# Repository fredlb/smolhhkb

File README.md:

# smolhhkb
A small 40% keyboard with same asymetrical bottom row as hhkb.

Pictured is a one-off prototype:  
Top: Polycarbonate  
Bottom: Aluminium, white anodization  
Weight: Copper  

The little window down to the PCB is resin printed, with an oring to attach it to the top piece.

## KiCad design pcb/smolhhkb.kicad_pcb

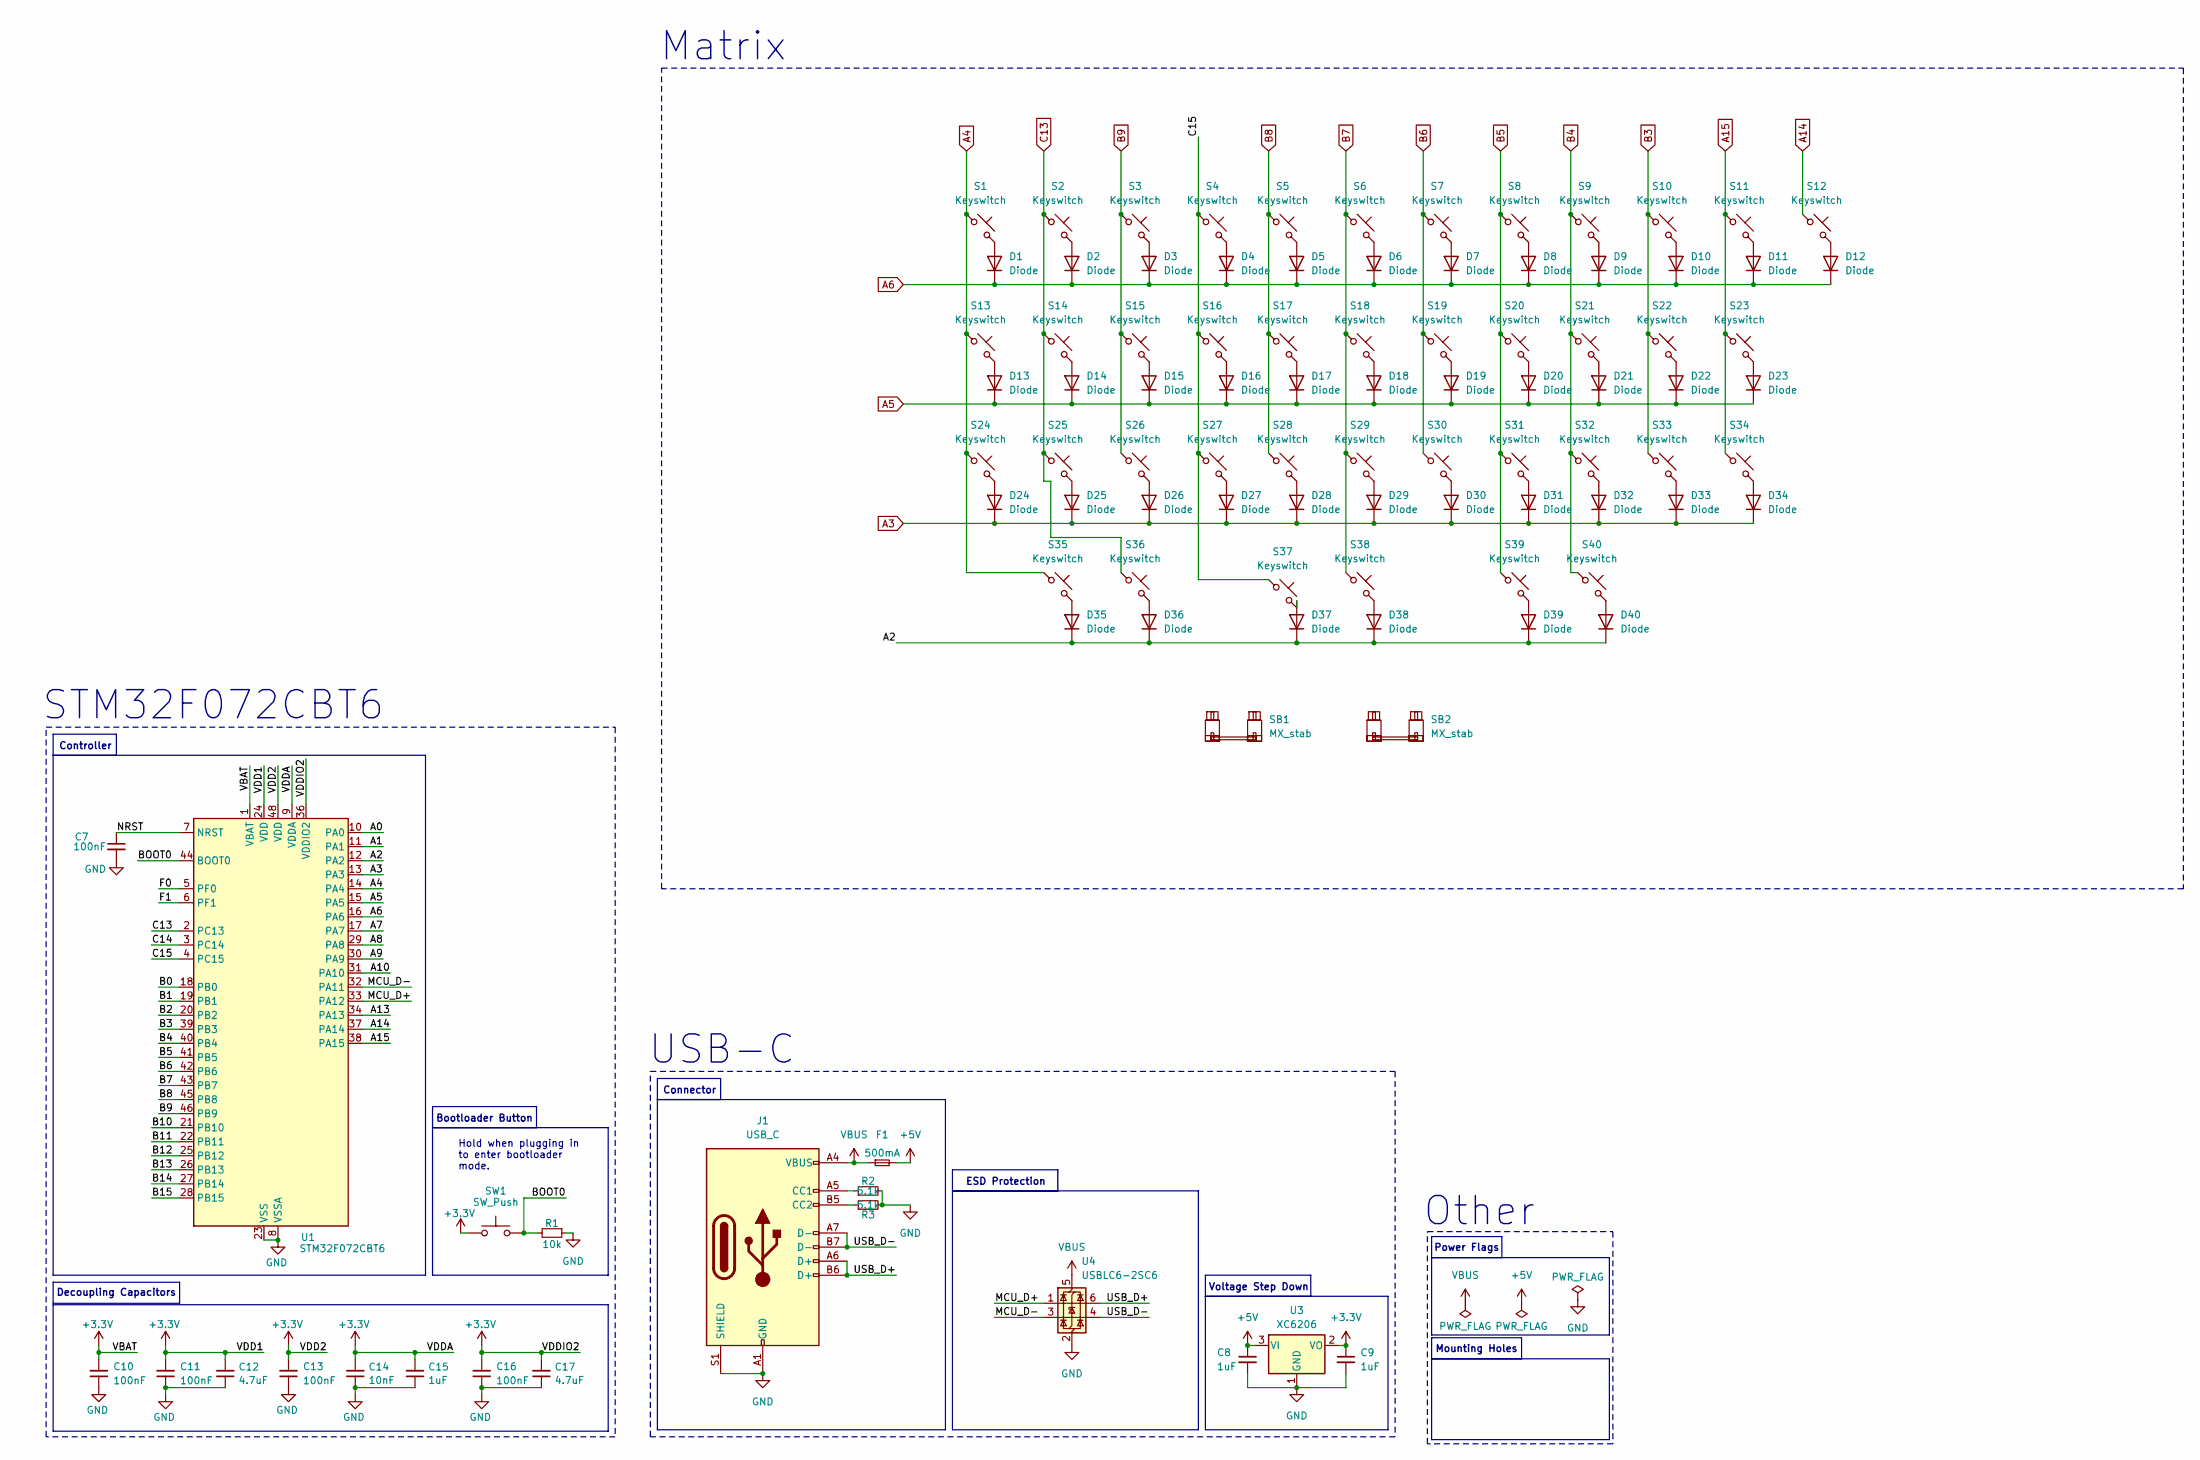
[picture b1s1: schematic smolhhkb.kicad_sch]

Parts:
C7: 100nF; Capacitor_0402; LCSC C307331
C8, C9: 1uF; Capacitor_0402; LCSC C52923
C10, C11, C13, C16: 100nF; Capacitor_0402; MPN CL05B104KB54PNC; LCSC C307331
C12, C17: 4.7uF; Capacitor_0402; MPN CL05A475MP5NRNC; LCSC C23733
C14: 10nF; Capacitor_0402; MPN CL05B103KB5NNNC; LCSC C15195
C15: 1uF; Capacitor_0402; MPN CL05A105KA5NQNC; LCSC C52923
D1, D2, D3, D4, D5, D6, D7, D8, D9, D10, D11, D12, D13, D14, D15, D16, D17, D18, D19, D20, D21, D22, D23, D24, D25, D26, D27, D28, D29, D30, D31, D32, D33, D34, D35, D36, D37, D38, D39, D40: Diode; Diode_SOD-123
F1: 500mA; Fuse_0603; LCSC C210357
J1: USB_C; USB_C_HRO_TYPE-C-31-M-12; LCSC C165948
R1: 10k; Resistor_0402; LCSC C25744
R2, R3: 5.1k; Resistor_0402; LCSC C25905
S1, S2, S3, S4, S5, S6, S7, S8, S9, S10, S11, S12, S14, S15, S16, S17, S18, S19, S20, S21, S22, S25, S26, S27, S28, S29, S30, S31, S32, S34, S35, S37, S38, S40: Keyswitch; SW_MX_1u
S13, S33, S36, S39: Keyswitch; SW_MX_1.25u
S23, S24: Keyswitch; SW_MX_1.75u
SB1: MX_stab; STAB_MX_2.25u
SB2: MX_stab; STAB_MX_2u
SW1: SW_Push; Button_TL3342; LCSC C115351
U1: STM32F072CBT6; Package_LQFP-48_7x7mm_P0.5; LCSC C81720
U3: XC6206; Voltage_SOT-23; LCSC C5446
U4: USBLC6-2SC6; ESD_SOT-23-6; LCSC C2827654

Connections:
+3.3V: C9.1, C10.2, C11.2, C12.2, C13.2, C14.2, C15.2, C16.2, C17.2, SW1.1, U1.1 (VBAT), U1.9 (VDDA), U1.24 (VDD), U1.36 (VDDIO2), U1.48 (VDD), U3.2 (VO)
+5V: C8.1, F1.2, U3.3 (VI)
/A0: U1.10 (PA0)
/A1: U1.11 (PA1)
/A2: D35.1 (K), D36.1 (K), D37.1 (K), D38.1 (K), D39.1 (K), D40.1 (K), U1.12 (PA2)
/A7: U1.17 (PA7)
/A8: U1.29 (PA8)
/A9: U1.30 (PA9)
/A10: U1.31 (PA10)
/A13: U1.34 (PA13)
/B0: U1.18 (PB0)
/B1: U1.19 (PB1)
/B2: U1.20 (PB2)
/B10: U1.21 (PB10)
/B11: U1.22 (PB11)
/B12: U1.25 (PB12)
/B13: U1.26 (PB13)
/B14: U1.27 (PB14)
/B15: U1.28 (PB15)
/BOOT0: R1.2, SW1.2, U1.44 (BOOT0)
/C14: U1.3 (PC14)
/C15: S4.1, S16.1, S27.1, S37.1, U1.4 (PC15)
/F0: U1.5 (PF0)
/F1: U1.6 (PF1)
/MCU_D+: U1.33 (PA12), U4.1 (I/O1)
/MCU_D-: U1.32 (PA11), U4.3 (I/O2)
/NRST: C7.1, U1.7 (NRST)
/USB_D+: J1.A6 (D+), J1.B6 (D+), U4.6 (I/O1)
/USB_D-: J1.A7 (D-), J1.B7 (D-), U4.4 (I/O2)
A3: D24.1 (K), D25.1 (K), D26.1 (K), D27.1 (K), D28.1 (K), D29.1 (K), D30.1 (K), D31.1 (K), D32.1 (K), D33.1 (K), D34.1 (K), U1.13 (PA3)
A4: S1.1, S13.1, S24.1, S35.1, U1.14 (PA4)
A5: D13.1 (K), D14.1 (K), D15.1 (K), D16.1 (K), D17.1 (K), D18.1 (K), D19.1 (K), D20.1 (K), D21.1 (K), D22.1 (K), D23.1 (K), U1.15 (PA5)
A6: D1.1 (K), D2.1 (K), D3.1 (K), D4.1 (K), D5.1 (K), D6.1 (K), D7.1 (K), D8.1 (K), D9.1 (K), D10.1 (K), D11.1 (K), D12.1 (K), U1.16 (PA6)
A14: S12.1, U1.37 (PA14)
A15: S11.1, S23.1, S34.1, U1.38 (PA15)
B3: S10.1, S22.1, S33.1, U1.39 (PB3)
B4: S9.1, S21.1, S32.1, S40.1, U1.40 (PB4)
B5: S8.1, S20.1, S31.1, S39.1, U1.41 (PB5)
B6: S7.1, S19.1, S30.1, U1.42 (PB6)
B7: S6.1, S18.1, S29.1, S38.1, U1.43 (PB7)
B8: S5.1, S17.1, S28.1, U1.45 (PB8)
B9: S3.1, S15.1, S26.1, U1.46 (PB9)
C13: S2.1, S14.1, S25.1, S36.1, U1.2 (PC13)
GND: C7.2, C8.2, C9.2, C10.1, C11.1, C12.1, C13.1, C14.1, C15.1, C16.1, C17.1, J1.A1 (GND), J1.A12 (GND), J1.B1 (GND), J1.B12 (GND), J1.S1 (SHIELD), R1.1, R2.2, R3.2, U1.8 (VSSA), U1.23 (VSS), U1.35 (VSS), U1.47 (VSS), U3.1 (GND), U4.2 (GND)
unnamed: D1.2 (A), S1.2
unnamed: D2.2 (A), S2.2
unnamed: D3.2 (A), S3.2
unnamed: D4.2 (A), S4.2
unnamed: D5.2 (A), S5.2
unnamed: D6.2 (A), S6.2
unnamed: D7.2 (A), S7.2
unnamed: D8.2 (A), S8.2
unnamed: D9.2 (A), S9.2
unnamed: D10.2 (A), S10.2
unnamed: D11.2 (A), S11.2
unnamed: D12.2 (A), S12.2
unnamed: D13.2 (A), S13.2
unnamed: D14.2 (A), S14.2
unnamed: D15.2 (A), S15.2
unnamed: D16.2 (A), S16.2
unnamed: D17.2 (A), S17.2
unnamed: D18.2 (A), S18.2
unnamed: D19.2 (A), S19.2
unnamed: D20.2 (A), S20.2
unnamed: D21.2 (A), S21.2
unnamed: D22.2 (A), S22.2
unnamed: D23.2 (A), S23.2
unnamed: D24.2 (A), S24.2
unnamed: D25.2 (A), S25.2
unnamed: D26.2 (A), S26.2
unnamed: D27.2 (A), S27.2
unnamed: D28.2 (A), S28.2
unnamed: D29.2 (A), S29.2
unnamed: D30.2 (A), S30.2
unnamed: D31.2 (A), S31.2
unnamed: D32.2 (A), S32.2
unnamed: D33.2 (A), S33.2
unnamed: D34.2 (A), S34.2
unnamed: D35.2 (A), S35.2
unnamed: D36.2 (A), S36.2
unnamed: D37.2 (A), S37.2
unnamed: D38.2 (A), S38.2
unnamed: D39.2 (A), S39.2
unnamed: D40.2 (A), S40.2
unnamed: J1.A5 (CC1), R2.1
unnamed: J1.B5 (CC2), R3.1
VBUS: F1.1, J1.A4 (VBUS), J1.A9 (VBUS), J1.B4 (VBUS), J1.B9 (VBUS), U4.5 (VBUS)

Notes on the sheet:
Hold when plugging in to enter bootloader mode.
STM32F072CBT6
USB-C
Mounting Holes
Decoupling Capacitors
Controller
ESD Protection
Power Flags
Voltage Step Down
Other
Bootloader Button
Matrix
Connector

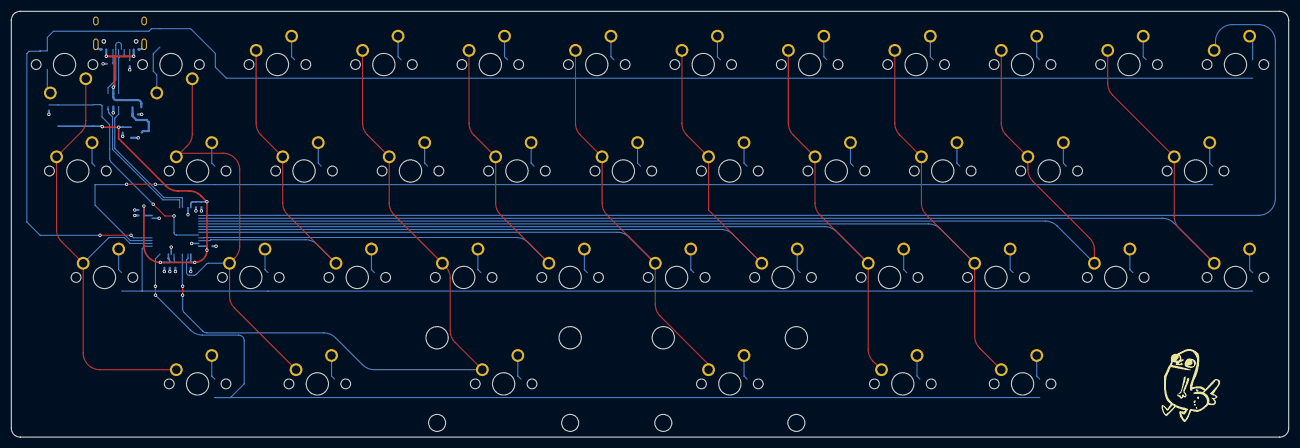
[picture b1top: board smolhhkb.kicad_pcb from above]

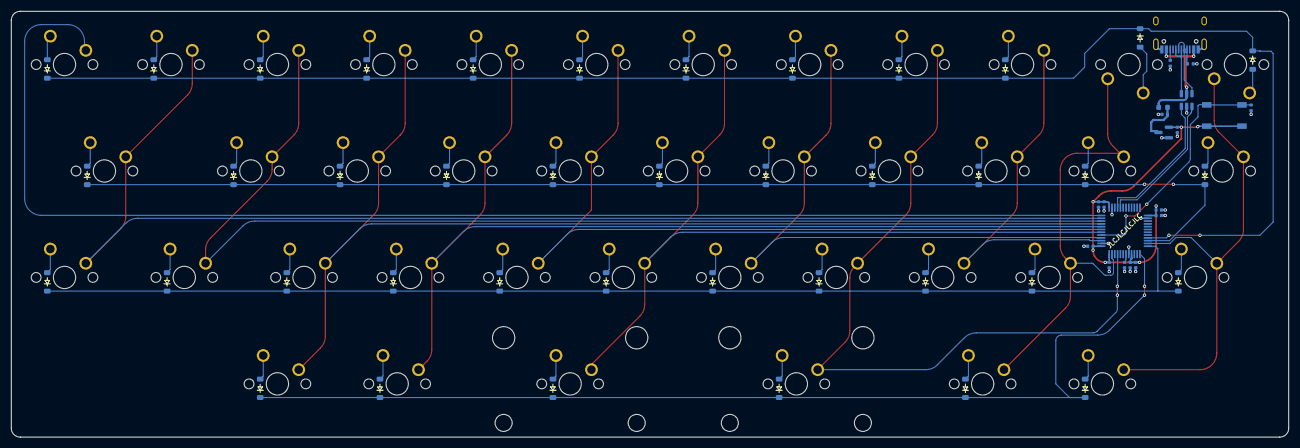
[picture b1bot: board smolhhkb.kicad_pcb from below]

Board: 4 copper layers, 228.6 x 76.2 mm, 102 parts (60 on the bottom side), 68 nets.

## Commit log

2024-07-23 init
2024-07-23 Fine tuning silkscreen placement
2025-01-24 case files
